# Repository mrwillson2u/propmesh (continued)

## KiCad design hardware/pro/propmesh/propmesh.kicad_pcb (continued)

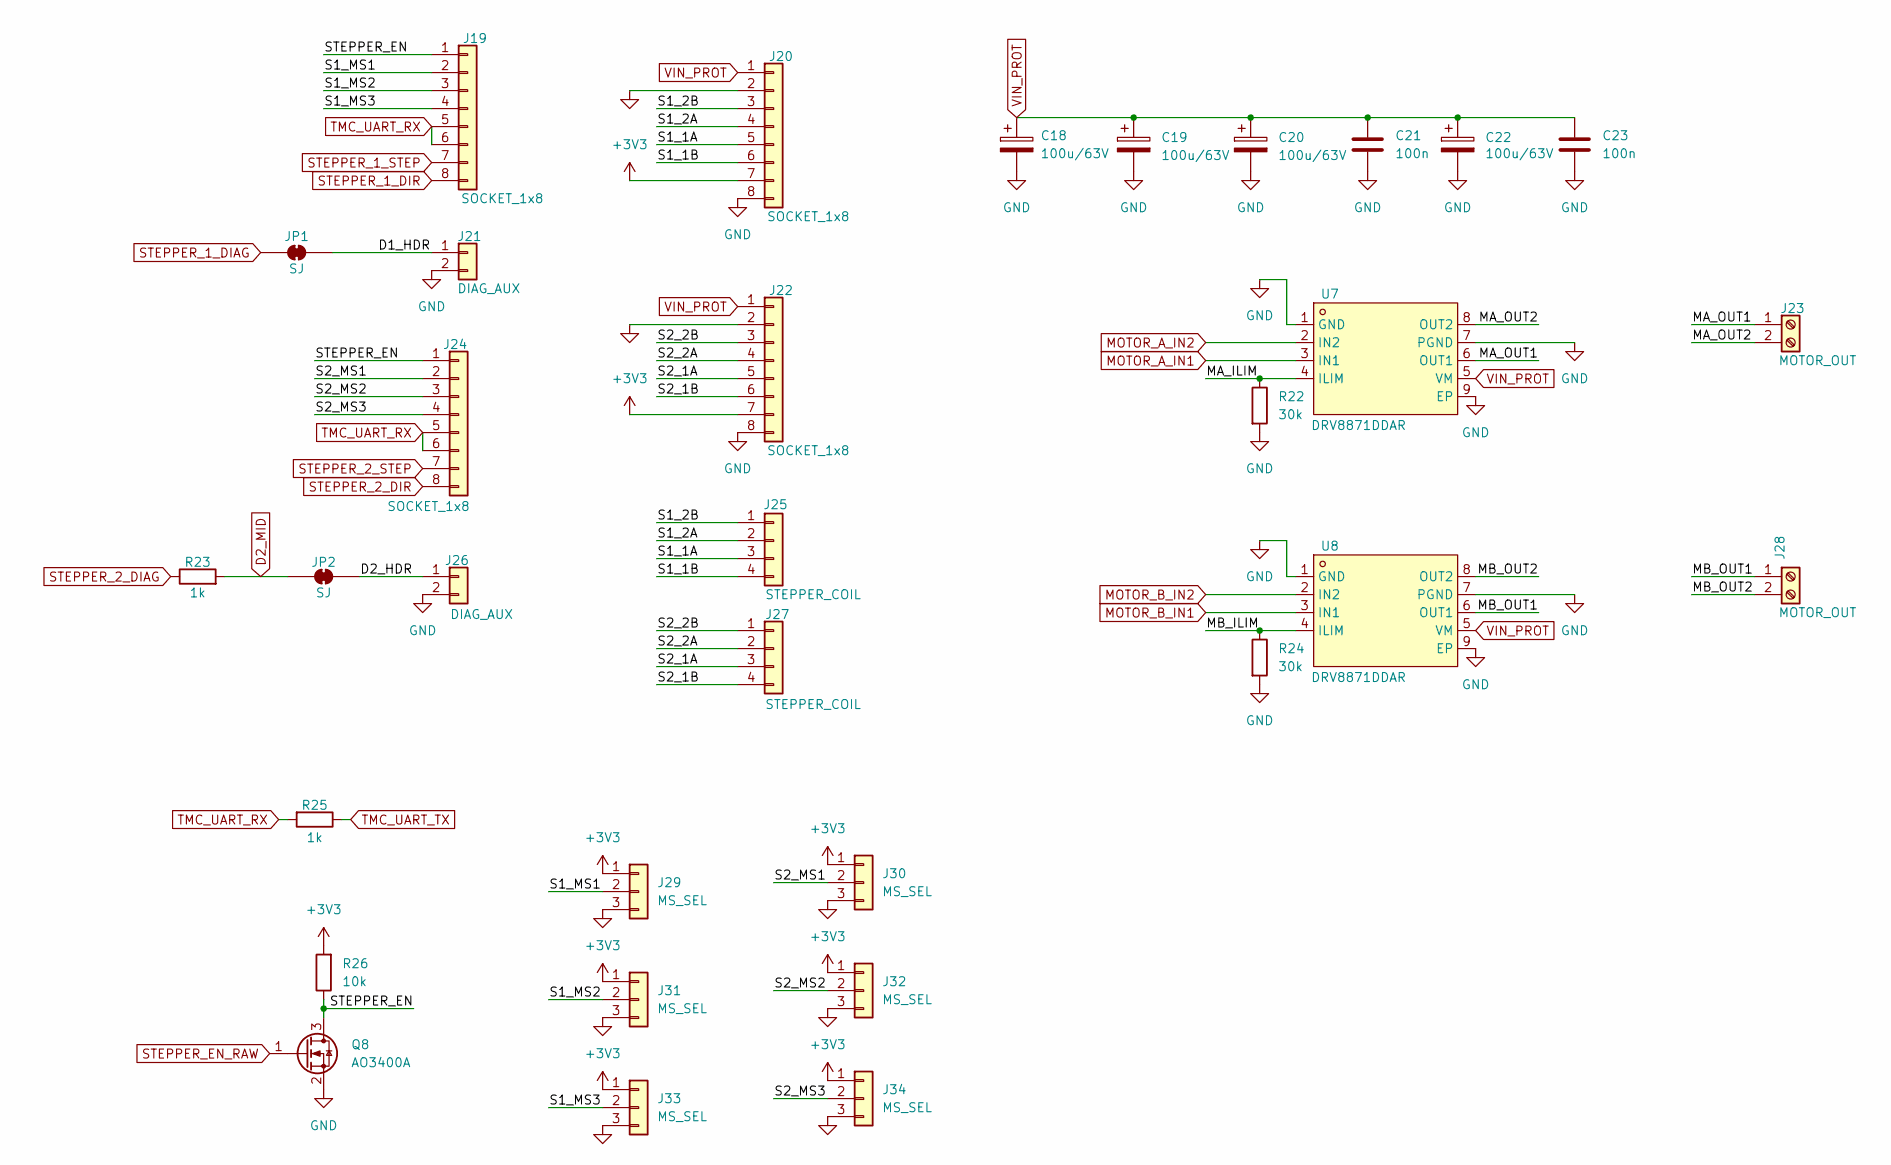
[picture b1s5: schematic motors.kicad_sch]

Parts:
C18, C19, C20, C22: 100u/63V; CP_Elec_8x10.5
C21, C23: 100n; C_0603_1608Metric
J19, J20, J22, J24: SOCKET_1x8; PinSocket_1x08_P2.54mm_Vertical
J21, J26: DIAG_AUX; PinHeader_1x02_P2.54mm_Vertical
J23, J28: MOTOR_OUT; CONN-TH_DG128-5.0-02P-14-00A-H
J25, J27: STEPPER_COIL; JST_XH_B4B-XH-A_1x04_P2.50mm_Vertical
J29, J30, J31, J32, J33, J34: MS_SEL; PinHeader_1x03_P2.54mm_Vertical
JP1, JP2: SJ; SolderJumper-2_P1.3mm_Bridged_RoundedPad1.0x1.5mm
Q8: AO3400A; SOT-23
R22, R24: 30k; R_0603_1608Metric
R23, R25: 1k; R_0603_1608Metric
R26: 10k; R_0603_1608Metric
U7, U8: DRV8871DDAR; SO-8EP_DRV8871DDAR; MPN DRV8871DDAR; LCSC Part C75864

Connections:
+3V3: J20.7, J22.7, J29.1, J30.1, J31.1, J32.1, J33.1, J34.1, R26.2; also elsewhere on the board
/Motors/D1_HDR: J21.1, JP1.2 (B)
/Motors/D2_HDR: J26.1, JP2.2 (B)
/Motors/MA_ILIM: R22.1, U7.4 (ILIM)
/Motors/MA_OUT1: J23.1, U7.6 (OUT1)
/Motors/MA_OUT2: J23.2, U7.8 (OUT2)
/Motors/MB_ILIM: R24.1, U8.4 (ILIM)
/Motors/MB_OUT1: J28.1, U8.6 (OUT1)
/Motors/MB_OUT2: J28.2, U8.8 (OUT2)
/Motors/S1_1A: J20.5, J25.3
/Motors/S1_1B: J20.6, J25.4
/Motors/S1_2A: J20.4, J25.2
/Motors/S1_2B: J20.3, J25.1
/Motors/S1_MS1: J19.2, J29.2
/Motors/S1_MS2: J19.3, J31.2
/Motors/S1_MS3: J19.4, J33.2
/Motors/S2_1A: J22.5, J27.3
/Motors/S2_1B: J22.6, J27.4
/Motors/S2_2A: J22.4, J27.2
/Motors/S2_2B: J22.3, J27.1
/Motors/S2_MS1: J24.2, J30.2
/Motors/S2_MS2: J24.3, J32.2
/Motors/S2_MS3: J24.4, J34.2
/Motors/STEPPER_EN: J19.1, J24.1, Q8.3 (D), R26.1
D2_MID: JP2.1 (A), R23.2; also elsewhere on the board
GND: C18.2, C19.2, C20.2, C21.2, C22.2, C23.2, J20.2, J20.8, J21.2, J22.2, J22.8, J26.2, J29.3, J30.3, J31.3, J32.3, J33.3, J34.3, Q8.2 (S), R22.2, R24.2, U7.1 (GND), U7.7 (PGND), U7.9 (EP), U8.1 (GND), U8.7 (PGND), U8.9 (EP); also elsewhere on the board
MOTOR_A_IN1: U7.3 (IN1); also elsewhere on the board
MOTOR_A_IN2: U7.2 (IN2); also elsewhere on the board
MOTOR_B_IN1: U8.3 (IN1); also elsewhere on the board
MOTOR_B_IN2: U8.2 (IN2); also elsewhere on the board
STEPPER_1_DIAG: JP1.1 (A); also elsewhere on the board
STEPPER_1_DIR: J19.8; also elsewhere on the board
STEPPER_1_STEP: J19.7; also elsewhere on the board
STEPPER_2_DIAG: R23.1; also elsewhere on the board
STEPPER_2_DIR: J24.8; also elsewhere on the board
STEPPER_2_STEP: J24.7; also elsewhere on the board
STEPPER_EN_RAW: Q8.1 (G); also elsewhere on the board
TMC_UART_RX: J19.5, J19.6, J24.5, J24.6, R25.2; also elsewhere on the board
TMC_UART_TX: R25.1; also elsewhere on the board
VIN_PROT: C18.1, C19.1, C20.1, C21.1, C22.1, C23.1, J20.1, J22.1, U7.5 (VM), U8.5 (VM); also elsewhere on the board

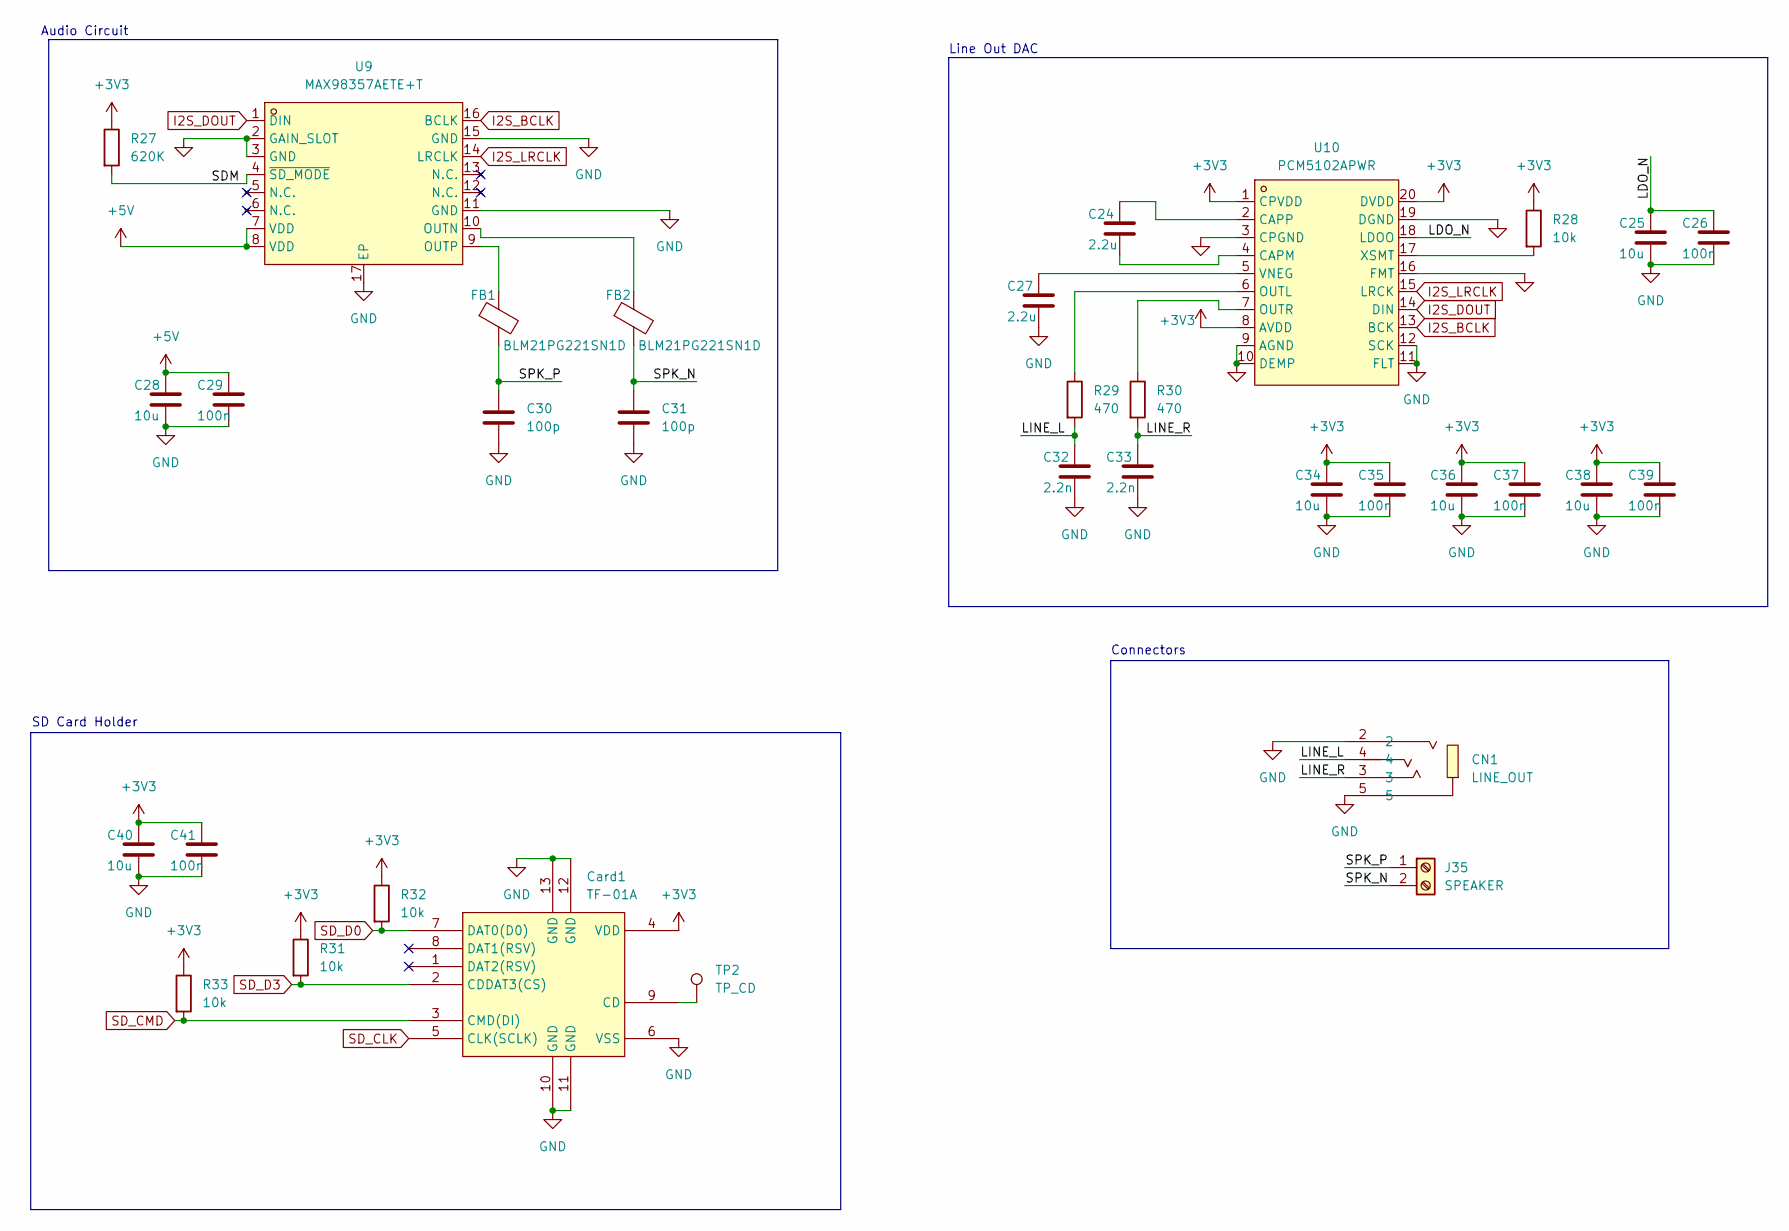
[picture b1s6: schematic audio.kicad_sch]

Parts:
C24, C27: 2.2u; C_0603_1608Metric
C25, C28, C34, C36, C38, C40: 10u; C_0805_2012Metric
C26, C29, C35, C37, C39, C41: 100n; C_0603_1608Metric
C30, C31: 100p; C_0603_1608Metric
C32, C33: 2.2n; C_0603_1608Metric
CN1: LINE_OUT; AUDIO-TH_XKB_PJ-320A; MPN PJ-320A; LCSC Part C2884926
Card1: TF-01A; TF-SMD_TF-01A; MPN TF-01A; LCSC Part C91145
FB1, FB2: BLM21PG221SN1D; L_0805_2012Metric
J35: SPEAKER; CONN-TH_DG381S-3.5-02P-14-00A-H
R27: 620K; R_0603_1608Metric
R28, R31, R32, R33: 10k; R_0603_1608Metric
R29, R30: 470; R_0603_1608Metric
TP2: TP_CD; TestPoint_Pad_1.5x1.5mm
U9: MAX98357AETE+T; TQFN-16_L3.0-W3.0-P0.50-BL-EP1.5; MPN MAX98357AETE+T; LCSC Part C910544
U10: PCM5102APWR; TSSOP-20_L6.5-W4.4-P0.65-LS6.4-BL; MPN PCM5102APWR; LCSC Part C107671

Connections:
+3V3: C34.1, C35.1, C36.1, C37.1, C38.1, C39.1, C40.1, C41.1, Card1.4 (VDD), R27.1, R28.1, R31.1, R32.1, R33.1, U10.1 (CPVDD), U10.8 (AVDD), U10.20 (DVDD); also elsewhere on the board
+5V: C28.1, C29.1, U9.7 (VDD), U9.8 (VDD); also elsewhere on the board
/Audio/LDO_N: C25.1, C26.1, U10.18 (LDOO)
/Audio/LINE_L: C32.1, CN1.4, R29.2
/Audio/LINE_R: C33.1, CN1.3, R30.2
/Audio/SDM: R27.2, U9.4 (~SD_MODE)
/Audio/SPK_N: C31.1, FB2.2, J35.2
/Audio/SPK_P: C30.1, FB1.2, J35.1
GND: C25.2, C26.2, C27.2, C28.2, C29.2, C30.2, C31.2, C32.2, C33.2, C34.2, C35.2, C36.2, C37.2, C38.2, C39.2, C40.2, C41.2, CN1.2, CN1.5, Card1.6 (VSS), Card1.10 (GND), Card1.11 (GND), Card1.12 (GND), Card1.13 (GND), U9.2 (GAIN_SLOT), U9.3 (GND), U9.11 (GND), U9.15 (GND), U9.17 (EP), U10.3 (CPGND), U10.9 (AGND), U10.10 (DEMP), U10.11 (FLT), U10.12 (SCK), U10.16 (FMT), U10.19 (DGND); also elsewhere on the board
I2S_BCLK: U9.16 (BCLK), U10.13 (BCK); also elsewhere on the board
I2S_DOUT: U9.1 (DIN), U10.14 (DIN); also elsewhere on the board
I2S_LRCLK: U9.14 (LRCLK), U10.15 (LRCK); also elsewhere on the board
unnamed: Card1.9 (CD), TP2.1 (1_1)
unnamed 114: Card1.8 (DAT1(RSV)); also elsewhere on the board
unnamed 115: Card1.1 (DAT2(RSV)); also elsewhere on the board
unnamed: FB2.1, U9.10 (OUTN)
unnamed: FB1.1, U9.9 (OUTP)
unnamed: C24.2, U10.4 (CAPM)
unnamed: C24.1, U10.2 (CAPP)
unnamed: R29.1, U10.6 (OUTL)
unnamed: R30.1, U10.7 (OUTR)
unnamed: C27.1, U10.5 (VNEG)
unnamed: R28.2, U10.17 (XSMT)
SD_CLK: Card1.5 (CLK(SCLK)); also elsewhere on the board
SD_CMD: Card1.3 (CMD(DI)), R33.2; also elsewhere on the board
SD_D0: Card1.7 (DAT0(D0)), R32.2; also elsewhere on the board
SD_D3: Card1.2 (CDDAT3(CS)), R31.2

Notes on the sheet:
Connectors
SD Card Holder
Line Out DAC
Audio Circuit

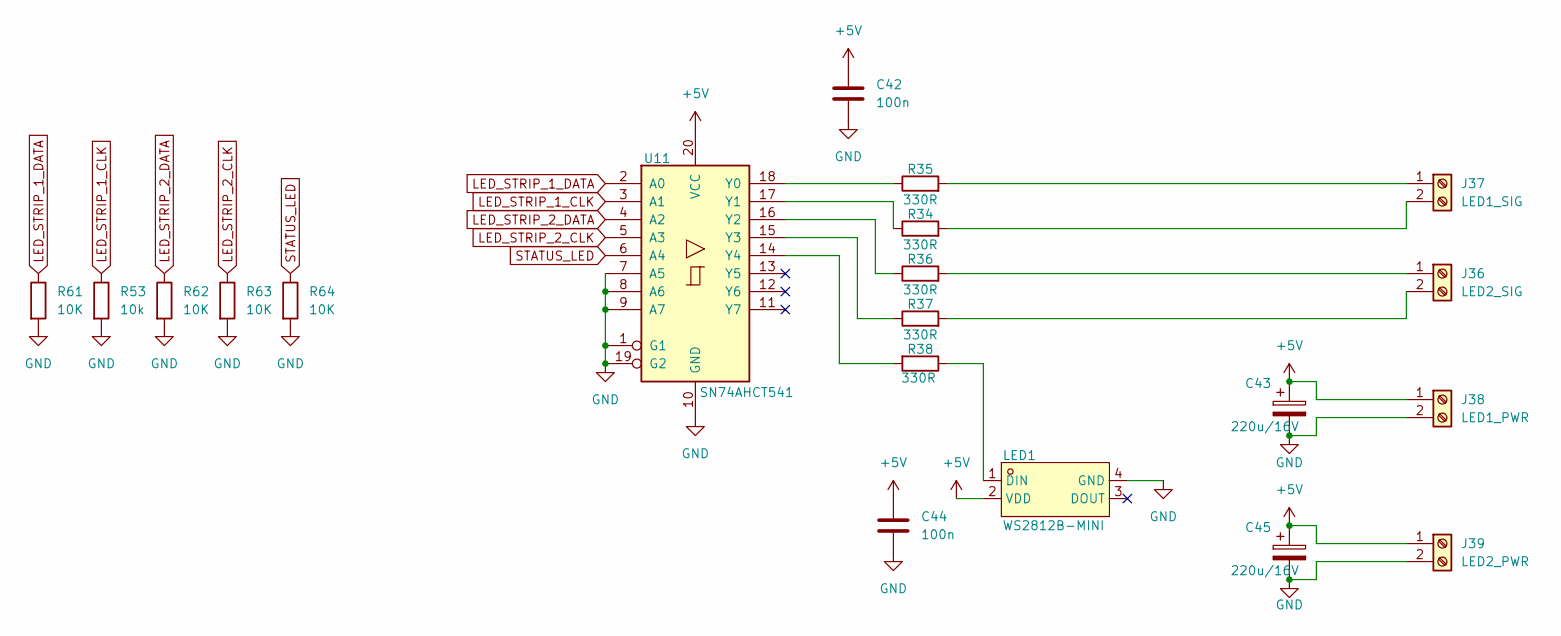
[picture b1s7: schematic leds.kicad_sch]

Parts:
C42, C44: 100n; C_0603_1608Metric
C43, C45: 220u/16V; CP_Radial_D6.3mm_P2.50mm
J36: LED2_SIG; CONN-TH_DG128-5.0-02P-14-00A-H
J37: LED1_SIG; CONN-TH_DG128-5.0-02P-14-00A-H
J38: LED1_PWR; CONN-TH_DG128-5.0-02P-14-00A-H
J39: LED2_PWR; CONN-TH_DG128-5.0-02P-14-00A-H
LED1: WS2812B-MINI; LED-SMD_4P-L3.5-W3.5-TL_WS2812B-1; MPN WS2812B-MINI-X2; LCSC Part C4154873
R34, R35, R36, R37, R38: 330R; R_0603_1608Metric
R53: 10k; R_0603_1608Metric
R61, R62, R63, R64: 10K; R_0603_1608Metric
U11: SN74AHCT541; SOIC-20W_7.5x12.8mm_P1.27mm

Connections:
+5V: C42.1, C43.1, C44.1, C45.1, J38.1, J39.1, LED1.2 (VDD), U11.20 (VCC); also elsewhere on the board
GND: C42.2, C43.2, C44.2, C45.2, J38.2, J39.2, LED1.4 (GND), R53.2, R61.2, R62.2, R63.2, R64.2, U11.1 (G1), U11.7 (A5), U11.8 (A6), U11.9 (A7), U11.10 (GND), U11.19 (G2); also elsewhere on the board
LED_STRIP_1_CLK: R53.1, U11.3 (A1); also elsewhere on the board
LED_STRIP_1_DATA: R61.1, U11.2 (A0); also elsewhere on the board
LED_STRIP_2_CLK: R63.1, U11.5 (A3); also elsewhere on the board
LED_STRIP_2_DATA: R62.1, U11.4 (A2); also elsewhere on the board
unnamed: J36.1, R36.2
unnamed: J36.2, R37.2
unnamed: J37.1, R35.2
unnamed: J37.2, R34.2
unnamed: LED1.1 (DIN), R38.1
unnamed: R35.1, U11.18 (Y0)
unnamed: R34.1, U11.17 (Y1)
unnamed: R36.1, U11.16 (Y2)
unnamed: R37.1, U11.15 (Y3)
unnamed: R38.2, U11.14 (Y4)
STATUS_LED: R64.1, U11.6 (A4); also elsewhere on the board

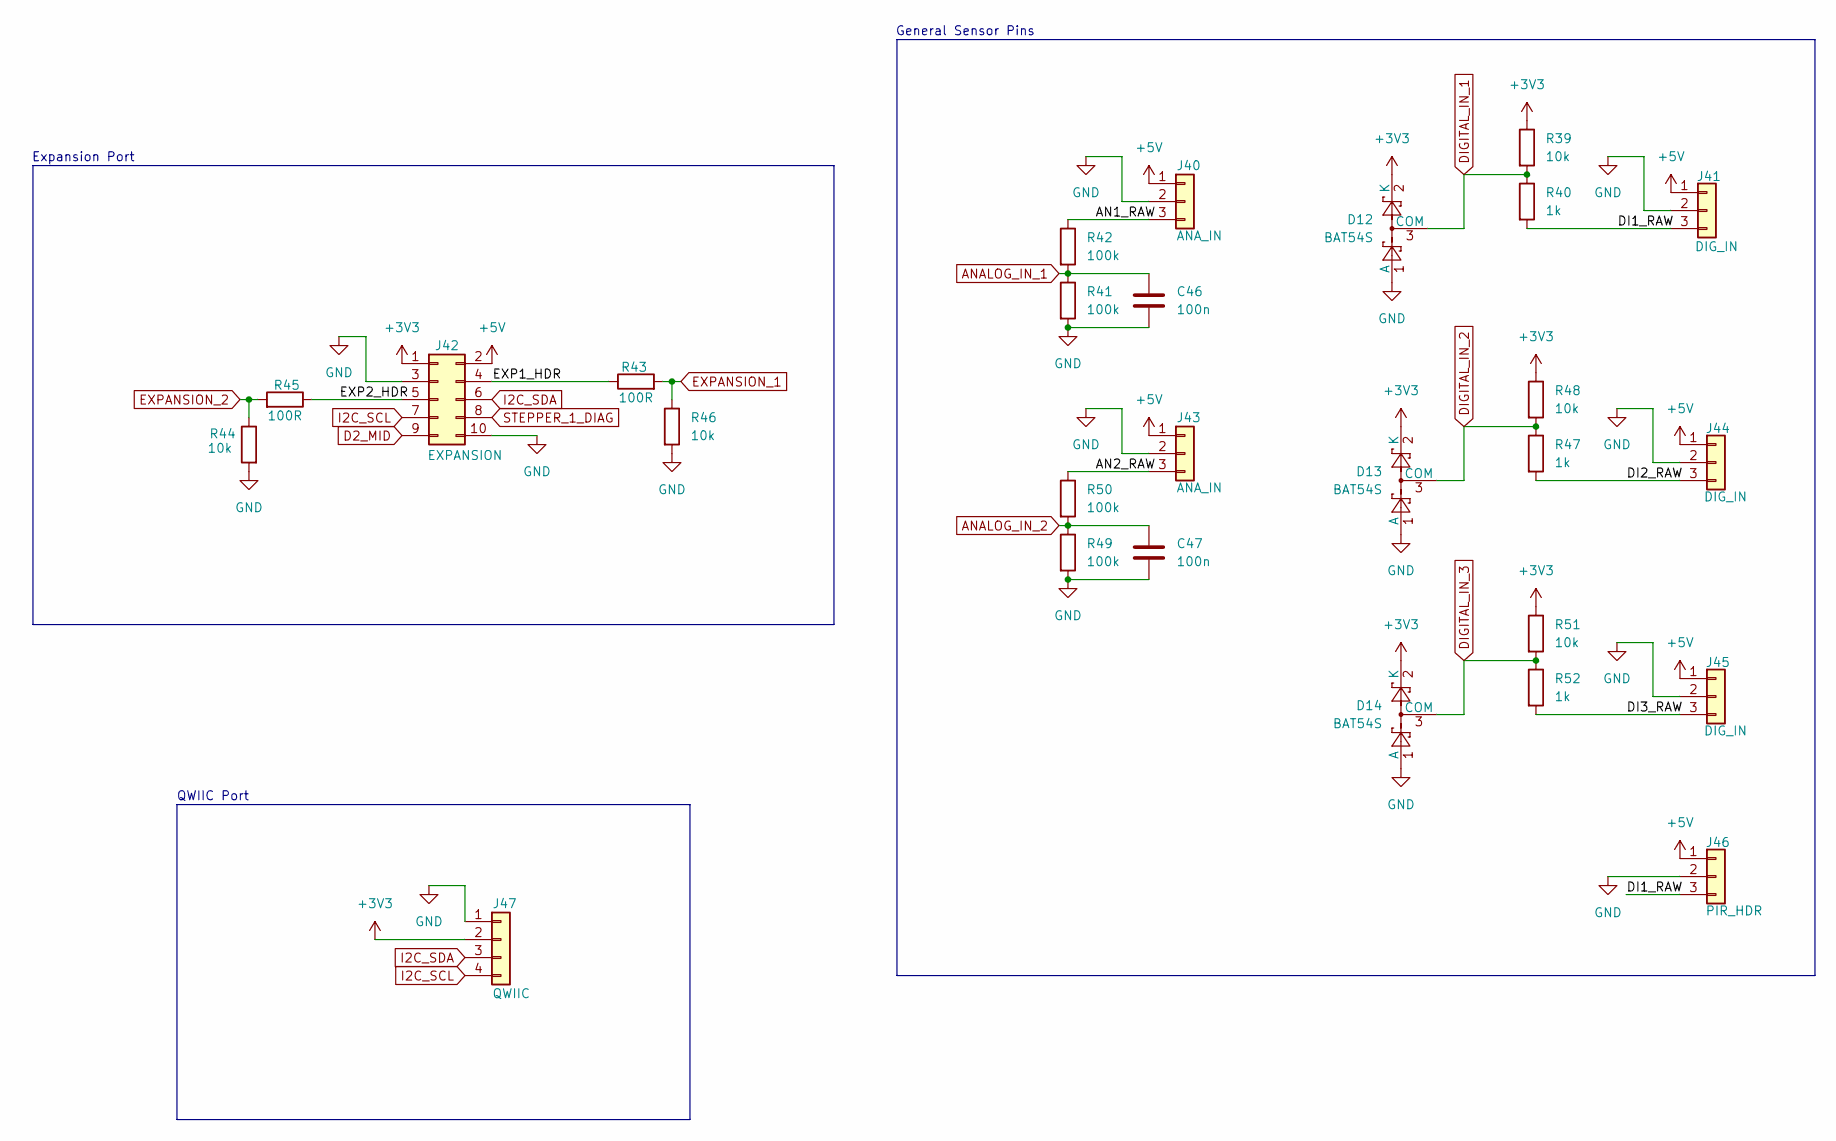
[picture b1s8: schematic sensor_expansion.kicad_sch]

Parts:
C46, C47: 100n; C_0603_1608Metric
D12, D13, D14: BAT54S; SOT-23
J40, J43: ANA_IN; JST_XH_B3B-XH-A_1x03_P2.50mm_Vertical
J41, J44, J45: DIG_IN; JST_XH_B3B-XH-A_1x03_P2.50mm_Vertical
J42: EXPANSION; PinHeader_2x05_P2.54mm_Vertical
J46: PIR_HDR; PinHeader_1x03_P2.54mm_Vertical
J47: QWIIC; JST_SH_SM04B-SRSS-TB_1x04-1MP_P1.00mm_Horizontal
R39, R44, R46, R48, R51: 10k; R_0603_1608Metric
R40, R47, R52: 1k; R_0603_1608Metric
R41, R42, R49, R50: 100k; R_0603_1608Metric
R43, R45: 100R; R_0603_1608Metric

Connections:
+3V3: D12.2 (K), D13.2 (K), D14.2 (K), J42.1, J47.2, R39.1, R48.1, R51.1; also elsewhere on the board
+5V: J40.1, J41.1, J42.2, J43.1, J44.1, J45.1, J46.1; also elsewhere on the board
/Sensor Expansion/AN1_RAW: J40.3, R42.1
/Sensor Expansion/AN2_RAW: J43.3, R50.1
/Sensor Expansion/DI1_RAW: J41.3, J46.3, R40.2
/Sensor Expansion/DI2_RAW: J44.3, R47.2
/Sensor Expansion/DI3_RAW: J45.3, R52.2
/Sensor Expansion/EXP1_HDR: J42.4, R43.1
/Sensor Expansion/EXP2_HDR: J42.5, R45.1
ANALOG_IN_1: C46.1, R41.1, R42.2; also elsewhere on the board
ANALOG_IN_2: C47.1, R49.1, R50.2; also elsewhere on the board
D2_MID: J42.9; also elsewhere on the board
DIGITAL_IN_1: D12.3 (COM), R39.2, R40.1; also elsewhere on the board
DIGITAL_IN_2: D13.3 (COM), R47.1, R48.2; also elsewhere on the board
DIGITAL_IN_3: D14.3 (COM), R51.2, R52.1; also elsewhere on the board
EXPANSION_1: R43.2, R46.1; also elsewhere on the board
EXPANSION_2: R44.1, R45.2; also elsewhere on the board
GND: C46.2, C47.2, D12.1 (A), D13.1 (A), D14.1 (A), J40.2, J41.2, J42.3, J42.10, J43.2, J44.2, J45.2, J46.2, J47.1, R41.2, R44.2, R46.2, R49.2; also elsewhere on the board
I2C_SCL: J42.7, J47.4; also elsewhere on the board
I2C_SDA: J42.6, J47.3; also elsewhere on the board
STEPPER_1_DIAG: J42.8; also elsewhere on the board

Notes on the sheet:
General Sensor Pins
QWIIC Port
Expansion Port

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
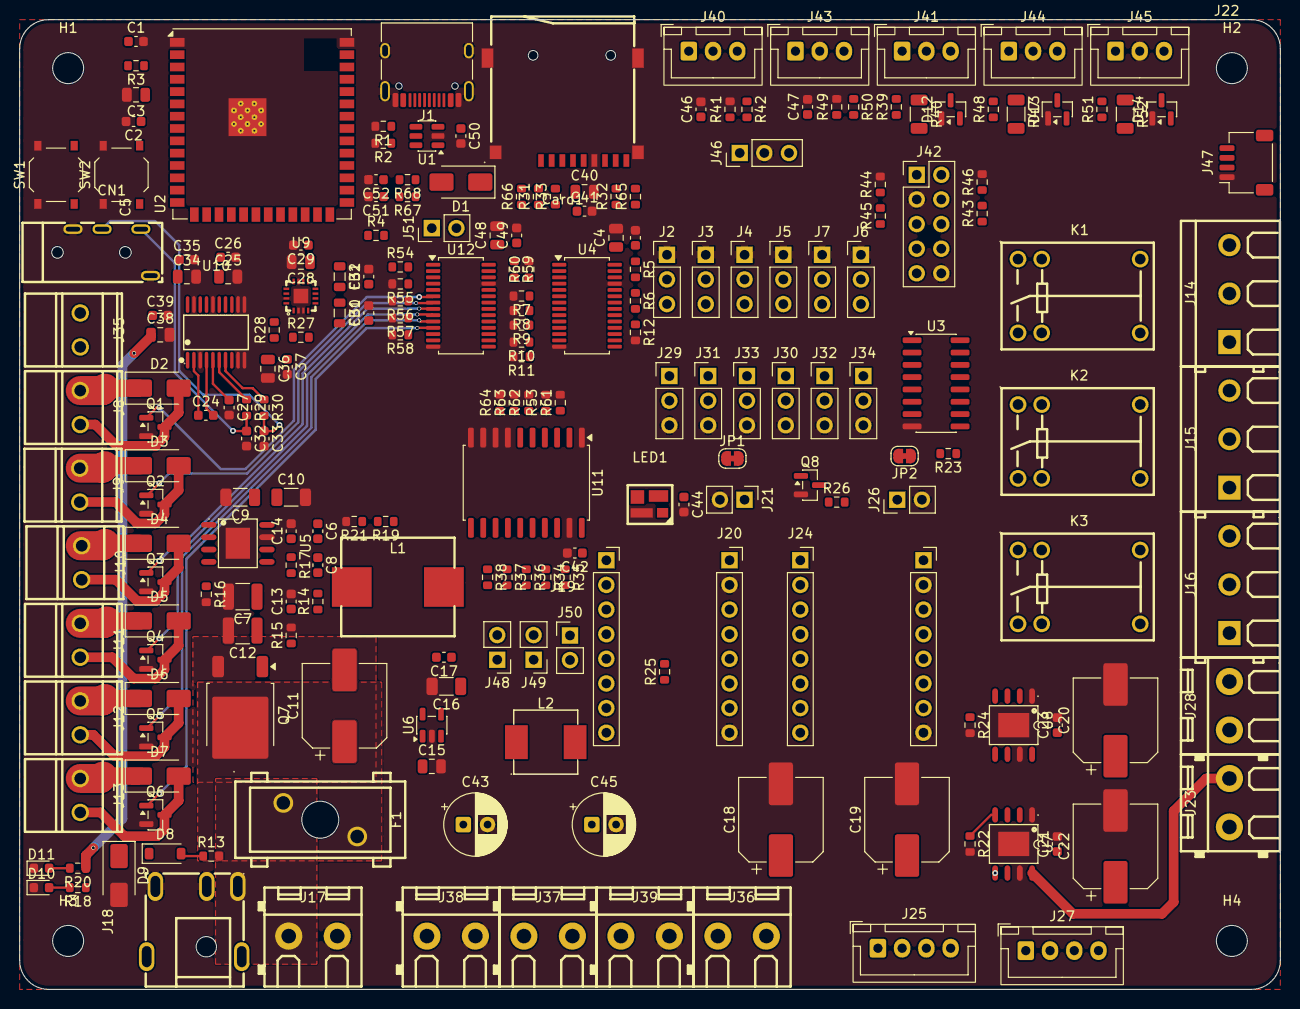
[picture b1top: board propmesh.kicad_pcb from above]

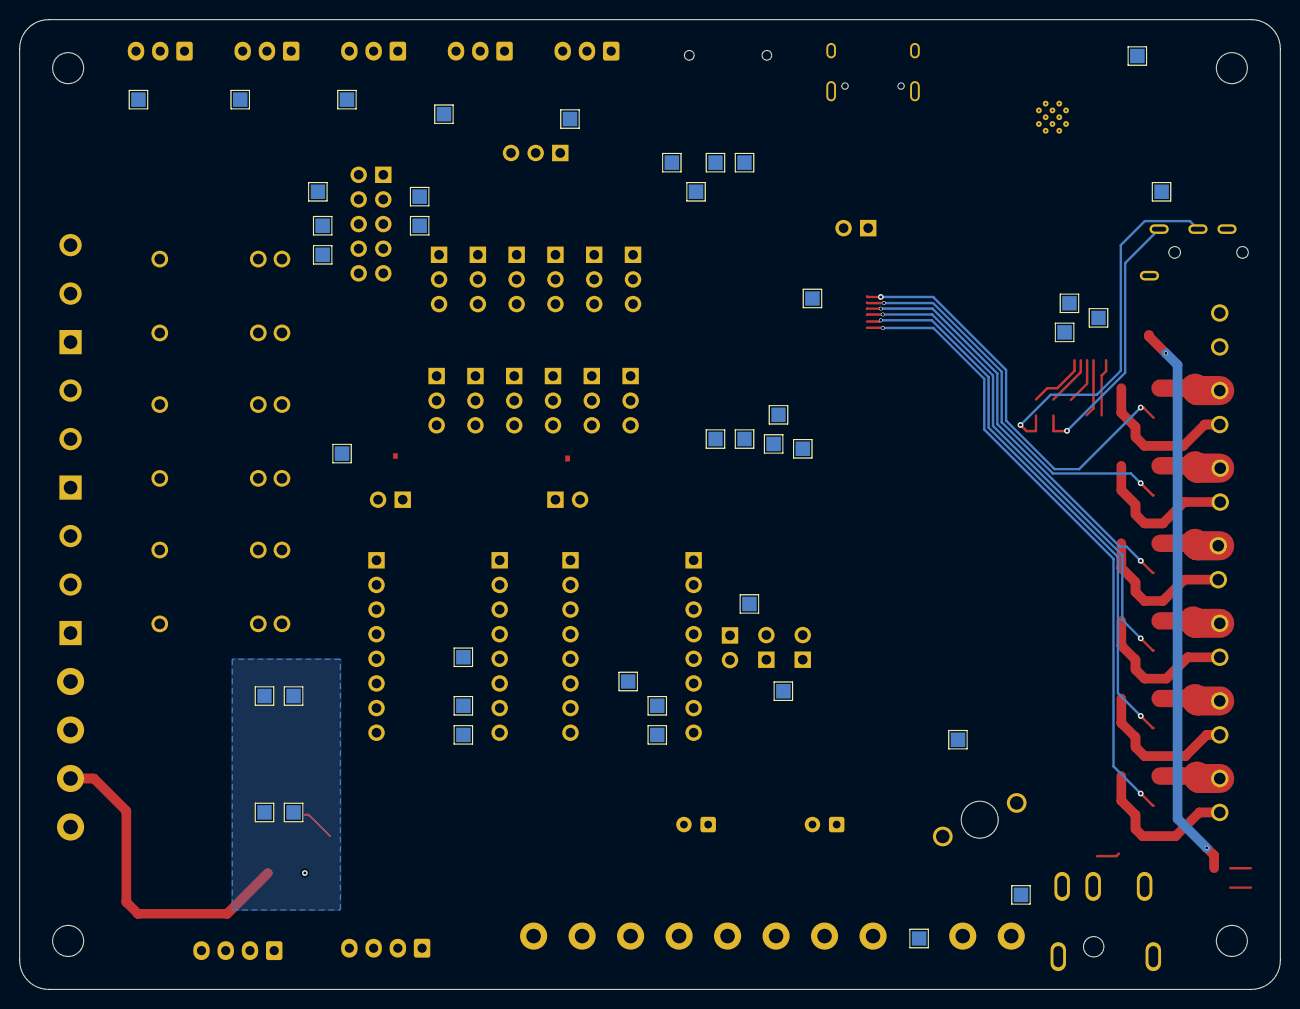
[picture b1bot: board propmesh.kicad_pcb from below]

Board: 4 copper layers, 130.0 x 100.0 mm, 265 parts (41 on the bottom side), 168 nets.

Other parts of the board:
C50: 100n; C_0603_1608Metric
C51, C52: DNP; C_0603_1608Metric
H1, H2, H3, H4: MountingHole_3.2mm_M3
J51: JP_USB; PinHeader_1x02_P2.54mm_Vertical
R65, R66: 10K; R_0603_1608Metric
R67, R68: 22R; R_0603_1608Metric

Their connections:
+3V3: R65.1, R66.1; also elsewhere on the board
+5V: J51.1; also elsewhere on the board
GND: C50.2, C51.2, C52.2; also elsewhere on the board
unnamed 114: R65.2; also elsewhere on the board
unnamed 115: R66.2; also elsewhere on the board
unnamed 116: J51.2; also elsewhere on the board
VBUS: C50.1; also elsewhere on the board

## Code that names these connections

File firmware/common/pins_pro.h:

// GENERATED FILE — DO NOT EDIT
// Source: pinmap.yaml   Regenerate: python3 tools/genpins.py

#ifndef PROPMESH_PINS_PRO_H
#define PROPMESH_PINS_PRO_H

// Board: pro   MCU: ESP32-S3-WROOM-1U-N8R2

#define PIN_BOOT_BUTTON           0  // strapping
#define PIN_ANALOG_IN_1           1  // ADC1 — ADC2 unusable with WiFi
#define PIN_ANALOG_IN_2           2  // ADC1
#define PIN_LED_STRIP_1_CLK       3  // APA102 CLK via the 74AHCT541 octal shifter; 3-/4-wire is a firmware setting (mode jumper dropped 2026-09-06). Was IR_RX until 2026-09-05 — onboard IR is useless on a hidden board; a plug-in receiver goes on any DIGITAL_IN. Strapping (JTAG select): drives only a shifter input. NOTE 2026-09-08: GPIO3 has NO internal pull — ESP32-S3 DS Table 3-1 lists it as Floating. It is safe only because the JTAG-select strap applies solely once the JTAG_SEL_ENABLE eFuse is burned. Populate R53 (the DNP pad on this net) to make it deterministic. See hardware/pro/review-2026-09-08.md
#define PIN_LED_STRIP_1_DATA      4  // RMT TX, via the 74AHCT541; APA102 DATA in 4-wire mode
#define PIN_LED_STRIP_2_DATA      5  // RMT TX, via the 74AHCT541; APA102 DATA in 4-wire mode
#define PIN_LED_STRIP_2_CLK       6  // APA102 CLK via the 74AHCT541; 3-/4-wire is a firmware setting (mode jumper dropped 2026-09-06)
#define PIN_I2S_BCLK              7
#define PIN_I2C_SDA               8  // PCA9685 + Qwiic
#define PIN_I2C_SCL               9
#define PIN_DIGITAL_IN_1          10  // pull-up, clamp diodes, 1k series
#define PIN_DIGITAL_IN_2          11
#define PIN_DIGITAL_IN_3          12
#define PIN_STEPPER_1_STEP        13  // LEDC-capable — required for DC socket mode
#define PIN_STEPPER_1_DIR         14  // LEDC-capable
#define PIN_I2S_LRCLK             15
#define PIN_I2S_DOUT              16
#define PIN_TMC_UART_TX           17  // shared bus, MS1/MS2 address strapping
#define PIN_TMC_UART_RX           18
#define PIN_USB_DM                19  // native USB — console lives here
#define PIN_USB_DP                20
#define PIN_STEPPER_2_STEP        21  // LEDC-capable
#define PIN_MOTOR_B_IN1           35  // LEDC 25 kHz. Moved from GPIO33 2026-09-03: 33/34 are NOT BONDED on any WROOM-1 (Espressif DS v1.8 pin table). 35 is free on N8R2, octal-PSRAM on R8/R16V
#define PIN_MOTOR_B_IN2           36  // LEDC 25 kHz. Moved from GPIO34 — same finding as MOTOR_B_IN1
#define PIN_PCA_OE                37  // both PCA9685 ~OE, 10k pull-up to 3V3: all PCA outputs held LOW (FETs, relays off; steppers disabled) while the MCU is in reset. Init the PCAs, THEN drive LOW. N8R2 only (octal PSRAM on R8/R16V)
#define PIN_STATUS_LED            38  // WS2812B-mini @ 5V — data via buffer 4 of the 74AHCT541
#define PIN_SD_CLK                39  // SDMMC 1-bit
#define PIN_SD_CMD                40  // 10k pull-up
#define PIN_SD_D0                 41  // 10k pull-up
#define PIN_STEPPER_1_DIAG        42  // StallGuard; JP1 frees it for expansion
#define PIN_STEPPER_2_DIAG        43  // StallGuard; JP2 frees it for expansion. U0TXD — ROM boot log drives it at reset; 1k series R
#define PIN_MOTOR_A_IN1           44  // LEDC 25 kHz
#define PIN_EXPANSION_1           45  // STRAPPING — must be LOW at reset. 10k pulldown + 100R series.
#define PIN_EXPANSION_2           46  // STRAPPING — must be LOW at reset. 10k pulldown + 100R series.
#define PIN_STEPPER_2_DIR         47  // LEDC-capable
#define PIN_MOTOR_A_IN2           48  // LEDC 25 kHz

#define PCA9685_COUNT 2
#define PCA9685_SERVO_ADDR 0x40
#define PCA9685_SERVO_HZ   50
#define PCA9685_DIM_ADDR 0x41
#define PCA9685_DIM_HZ   1000

// PCA9685_SERVO (0x40)
#define PCA_SERVO_1             0
#define PCA_SERVO_1_ADDR        PCA9685_SERVO_ADDR
#define PCA_SERVO_2             1
#define PCA_SERVO_2_ADDR        PCA9685_SERVO_ADDR
#define PCA_SERVO_3             2
#define PCA_SERVO_3_ADDR        PCA9685_SERVO_ADDR
#define PCA_SERVO_4             3
#define PCA_SERVO_4_ADDR        PCA9685_SERVO_ADDR
#define PCA_SERVO_5             4
#define PCA_SERVO_5_ADDR        PCA9685_SERVO_ADDR
#define PCA_SERVO_6             5
#define PCA_SERVO_6_ADDR        PCA9685_SERVO_ADDR
#define PCA_RELAY_1             12
#define PCA_RELAY_1_ADDR        PCA9685_SERVO_ADDR
#define PCA_RELAY_2             13
#define PCA_RELAY_2_ADDR        PCA9685_SERVO_ADDR
#define PCA_RELAY_3             14
#define PCA_RELAY_3_ADDR        PCA9685_SERVO_ADDR
#define PCA_STEPPER_ENABLE      15
#define PCA_STEPPER_ENABLE_ADDR PCA9685_SERVO_ADDR

// PCA9685_DIM (0x41)
#define PCA_LED_1               0
#define PCA_LED_1_ADDR          PCA9685_DIM_ADDR
#define PCA_LED_2               1
#define PCA_LED_2_ADDR          PCA9685_DIM_ADDR
#define PCA_LED_3               2
#define PCA_LED_3_ADDR          PCA9685_DIM_ADDR
#define PCA_LED_4               3
#define PCA_LED_4_ADDR          PCA9685_DIM_ADDR
#define PCA_LED_5               4
#define PCA_LED_5_ADDR          PCA9685_DIM_ADDR
#define PCA_LED_6               5
#define PCA_LED_6_ADDR          PCA9685_DIM_ADDR

#define MOTOR_PWM_HZ 25000
#define SERVO_PWM_HZ 50
#define LED_PWM_HZ 1000

#endif  // PROPMESH_PINS_PRO_H
